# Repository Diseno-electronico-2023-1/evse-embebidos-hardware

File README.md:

# evse-embebidos-hardware
Cada grupo crea una rama para su PCB, cuando acaben hacen merge a la rama

Para crear una rama:

git checkout -b branch-name

Donde branch-name es el nombre de la rama Ej: Potencia

Una vez que estan en la nueva rama pueden subir sus cambios con:

git add .

git commit -m "Descripción de sus cambios"

git push -u origin branch-name

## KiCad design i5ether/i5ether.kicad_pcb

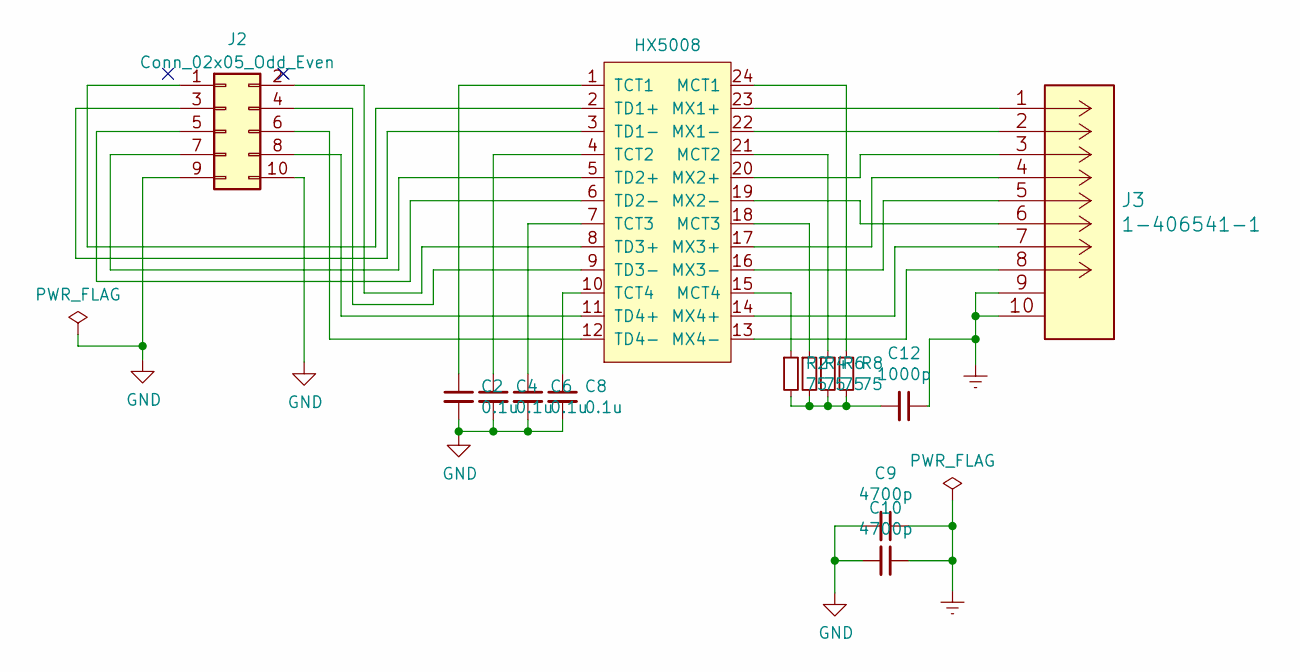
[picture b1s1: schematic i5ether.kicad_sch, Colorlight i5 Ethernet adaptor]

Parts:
C2, C4, C6, C8: 0.1u; C_0402_1005Metric
C9, C10: 4700p; R_1812_4532Metric
C12: 1000p; C_0402_1005Metric
J2: Conn_02x05_Odd_Even; PinHeader_2x05_P2.54mm_Horizontal
J3: 1-406541-1
R2, R4, R6, R8: 75; R_0402_1005Metric
T2: HX5008; HX5008NL

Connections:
Earth: C9.1, C10.1, C12.1, J3.9 (SHIELD), J3.10 (SHIELD)
GND: C2.2, C4.2, C6.2, C8.2, C9.2, C10.2, J2.9, J2.10
unnamed: C12.2, R2.2, R4.2, R6.2, R8.2
unnamed: J2.1, T2.2 (TD1+)
unnamed: J2.2, T2.8 (TD3+)
unnamed: J2.3, T2.3 (TD1-)
unnamed: J2.4, T2.9 (TD3-)
unnamed: J2.5, T2.6 (TD2-)
unnamed: J2.6, T2.12 (TD4-)
unnamed: J2.7, T2.5 (TD2+)
unnamed: J2.8, T2.11 (TD4+)
unnamed: R8.1, T2.24 (MCT1)
unnamed: R6.1, T2.21 (MCT2)
unnamed: R4.1, T2.18 (MCT3)
unnamed: R2.1, T2.15 (MCT4)
unnamed: J3.1, T2.23 (MX1+)
unnamed: J3.2, T2.22 (MX1-)
unnamed: J3.3, T2.20 (MX2+)
unnamed: J3.6, T2.19 (MX2-)
unnamed: J3.4, T2.17 (MX3+)
unnamed: J3.5, T2.16 (MX3-)
unnamed: J3.7, T2.14 (MX4+)
unnamed: J3.8, T2.13 (MX4-)
unnamed: C2.1, T2.1 (TCT1)
unnamed: C4.1, T2.4 (TCT2)
unnamed: C6.1, T2.7 (TCT3)
unnamed: C8.1, T2.10 (TCT4)

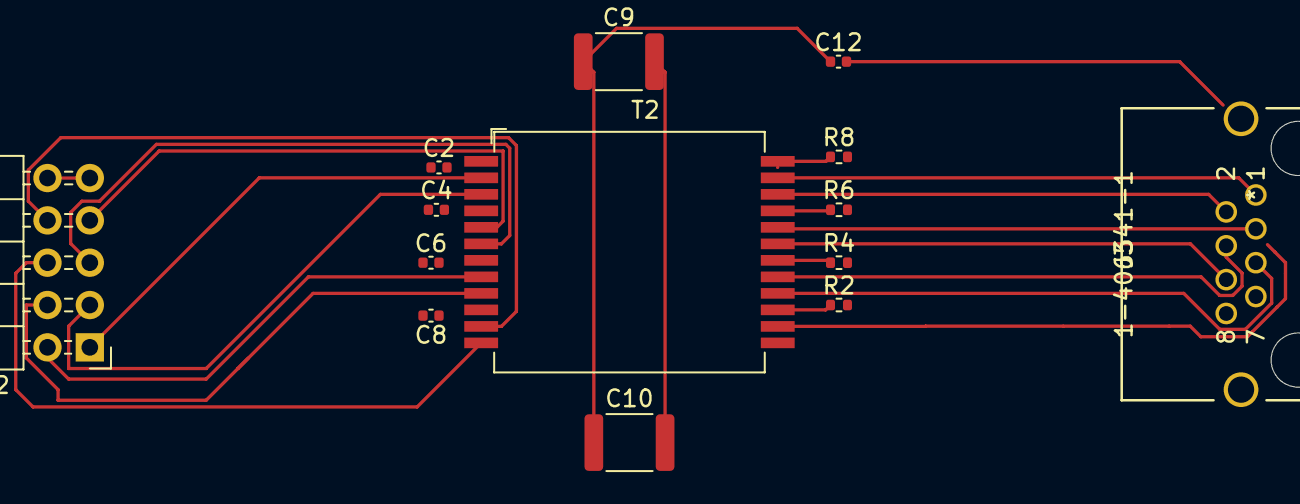
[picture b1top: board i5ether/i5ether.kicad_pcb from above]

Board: 2 copper layers, 14 parts (0 on the bottom side), 27 nets.

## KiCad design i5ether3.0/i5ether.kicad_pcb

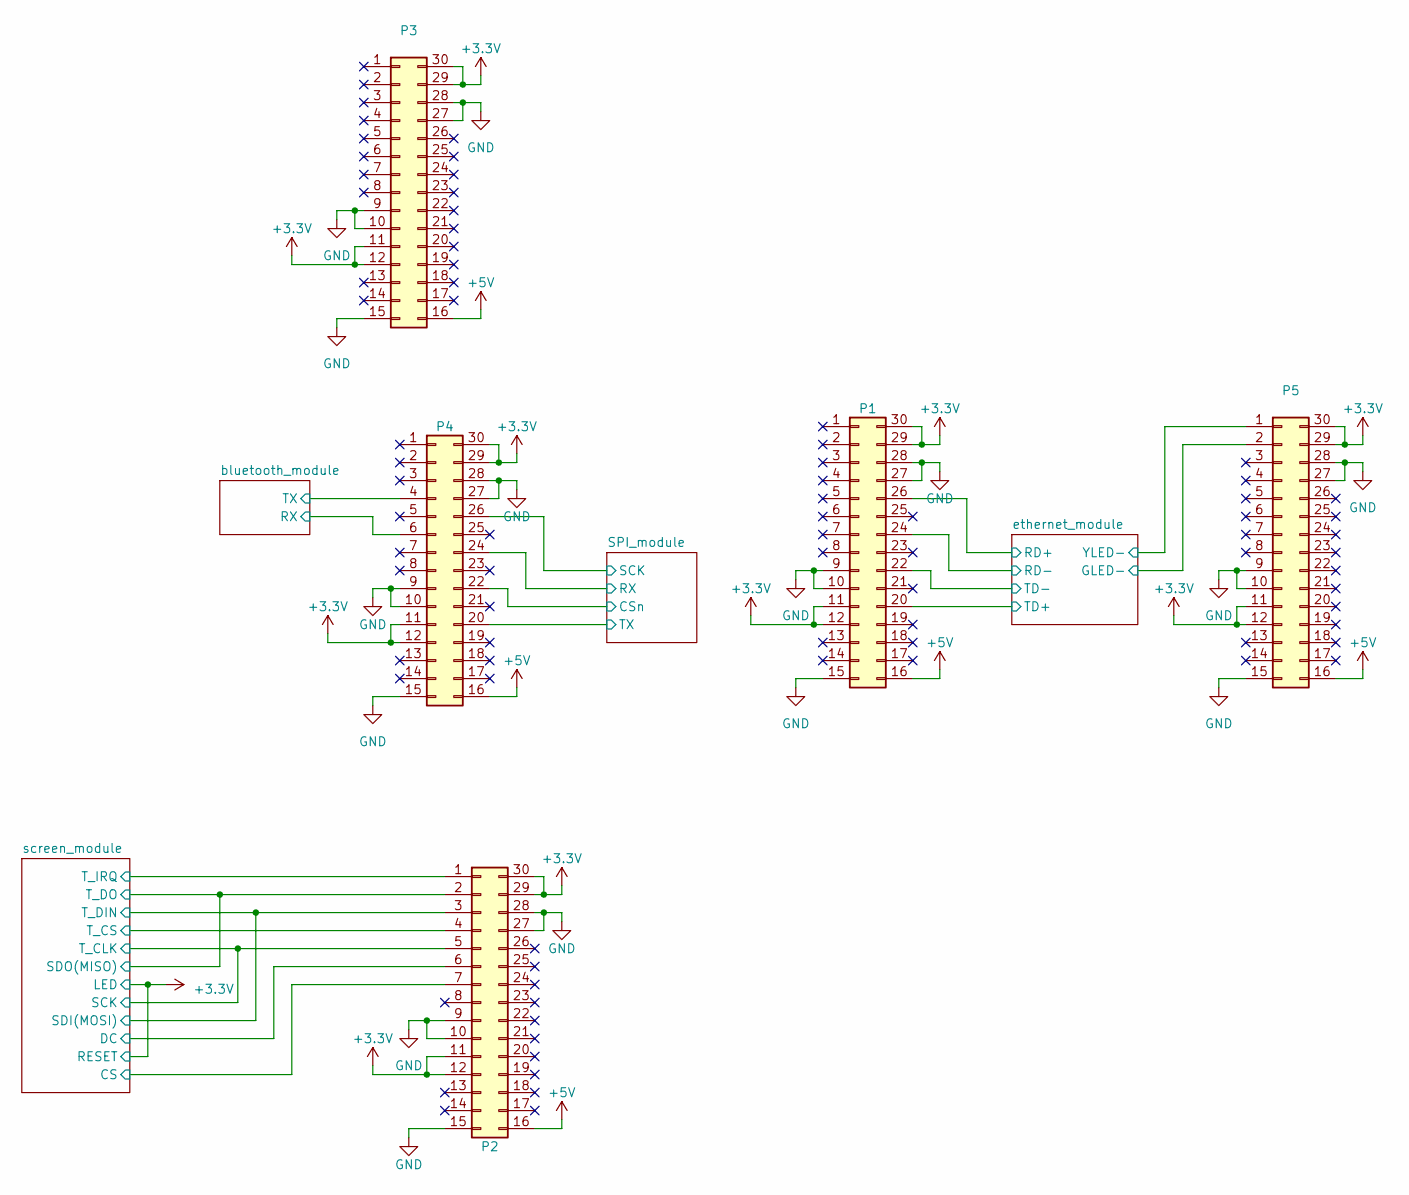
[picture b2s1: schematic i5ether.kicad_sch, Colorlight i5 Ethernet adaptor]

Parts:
P1, P2, P3, P4, P5: Conn_02x15_Counter_Clockwise; PinHeader_2x15_P2.54mm_Vertical

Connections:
+3.3V: P1.11, P1.12, P1.29, P1.30, P2.11, P2.12, P2.29, P2.30, P3.11, P3.12, P3.29, P3.30, P4.11, P4.12, P4.29, P4.30, P5.11, P5.12, P5.29, P5.30; also elsewhere on the board
+5V: P1.16, P2.16, P3.16, P4.16, P5.16
/SPI_module/CSn: P4.22; also elsewhere on the board
/SPI_module/RX: P4.24; also elsewhere on the board
/SPI_module/SCK: P4.26; also elsewhere on the board
/SPI_module/TX: P4.20; also elsewhere on the board
/bluetooth_module/RX: P4.6; also elsewhere on the board
/bluetooth_module/TX: P4.4; also elsewhere on the board
/ethernet_module/GLED-: P5.2; also elsewhere on the board
/ethernet_module/RD+: P1.26; also elsewhere on the board
/ethernet_module/RD-: P1.24; also elsewhere on the board
/ethernet_module/TD+: P1.20; also elsewhere on the board
/ethernet_module/TD-: P1.22; also elsewhere on the board
/ethernet_module/YLED-: P5.1; also elsewhere on the board
/screen_module/CS: P2.7; also elsewhere on the board
/screen_module/DC: P2.6; also elsewhere on the board
/screen_module/SCK: P2.5; also elsewhere on the board
/screen_module/SDI(MOSI): P2.3; also elsewhere on the board
/screen_module/SDO(MISO): P2.2; also elsewhere on the board
/screen_module/T_CS: P2.4; also elsewhere on the board
/screen_module/T_IRQ: P2.1; also elsewhere on the board
GND: P1.9, P1.10, P1.15, P1.27, P1.28, P2.9, P2.10, P2.15, P2.27, P2.28, P3.9, P3.10, P3.15, P3.27, P3.28, P4.9, P4.10, P4.15, P4.27, P4.28, P5.9, P5.10, P5.15, P5.27, P5.28; also elsewhere on the board

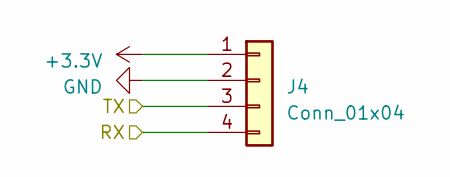
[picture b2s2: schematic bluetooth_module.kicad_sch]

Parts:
J4: Conn_01x04; PinSocket_1x04_P2.54mm_Horizontal

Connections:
+3.3V: J4.1; also elsewhere on the board
/bluetooth_module/RX: J4.4; also elsewhere on the board
/bluetooth_module/TX: J4.3; also elsewhere on the board
GND: J4.2; also elsewhere on the board

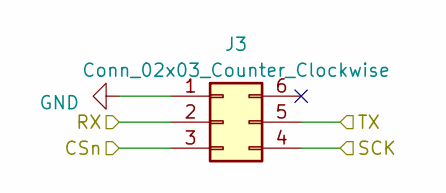
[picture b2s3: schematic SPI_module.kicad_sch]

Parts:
J3: Conn_02x03_Counter_Clockwise; IDC-Header_2x04_P2.54mm_Vertical

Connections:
/SPI_module/CSn: J3.3; also elsewhere on the board
/SPI_module/RX: J3.2; also elsewhere on the board
/SPI_module/SCK: J3.4; also elsewhere on the board
/SPI_module/TX: J3.5; also elsewhere on the board
GND: J3.1; also elsewhere on the board

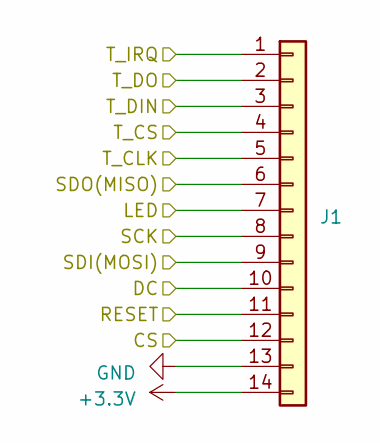
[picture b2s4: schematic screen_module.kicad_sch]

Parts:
J1: Conn_01x14; IDC-Header_2x08-1MP_P2.54mm_Latch6.5mm_Vertical

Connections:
+3.3V: J1.7, J1.11, J1.14; also elsewhere on the board
/screen_module/CS: J1.12; also elsewhere on the board
/screen_module/DC: J1.10; also elsewhere on the board
/screen_module/SCK: J1.5, J1.8; also elsewhere on the board
/screen_module/SDI(MOSI): J1.3, J1.9; also elsewhere on the board
/screen_module/SDO(MISO): J1.2, J1.6; also elsewhere on the board
/screen_module/T_CS: J1.4; also elsewhere on the board
/screen_module/T_IRQ: J1.1; also elsewhere on the board
GND: J1.13; also elsewhere on the board

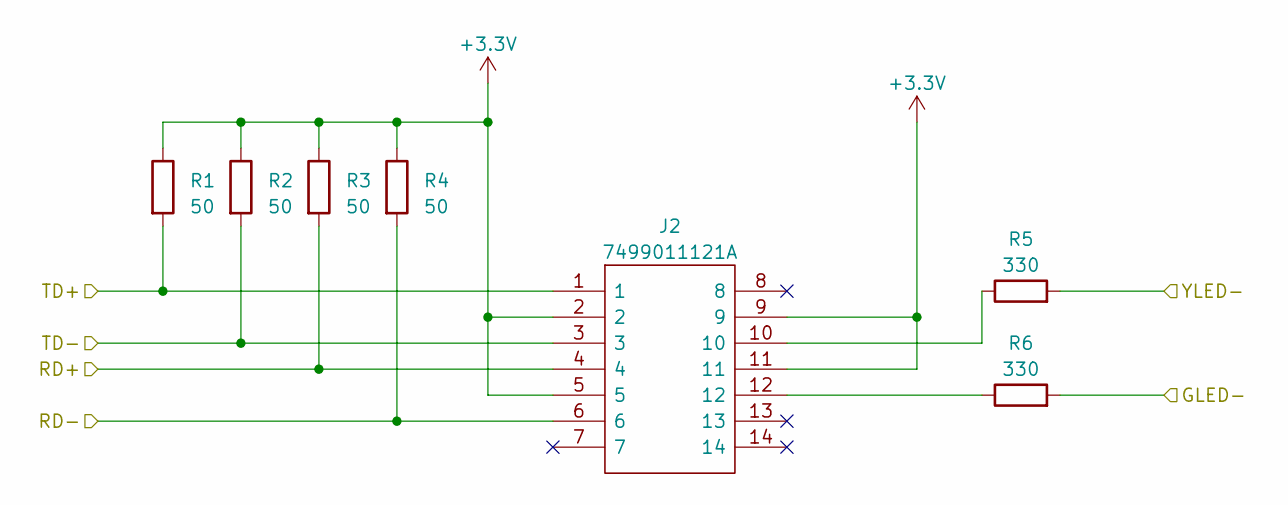
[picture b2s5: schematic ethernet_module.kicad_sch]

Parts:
J2: 7499011121A; Mouser Part Number 710-7499011121A
R1, R2, R3, R4: 50; R_0603_1608Metric_Pad0.98x0.95mm_HandSolder
R5, R6: 330; R_0603_1608Metric_Pad0.98x0.95mm_HandSolder

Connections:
+3.3V: J2.2, J2.5, J2.9, J2.11, R1.1, R2.1, R3.1, R4.1; also elsewhere on the board
/ethernet_module/GLED-: R6.2; also elsewhere on the board
/ethernet_module/RD+: J2.4, R3.2; also elsewhere on the board
/ethernet_module/RD-: J2.6, R4.2; also elsewhere on the board
/ethernet_module/TD+: J2.1, R1.2; also elsewhere on the board
/ethernet_module/TD-: J2.3, R2.2; also elsewhere on the board
/ethernet_module/YLED-: R5.2; also elsewhere on the board
unnamed: J2.10, R5.1
unnamed: J2.12, R6.1

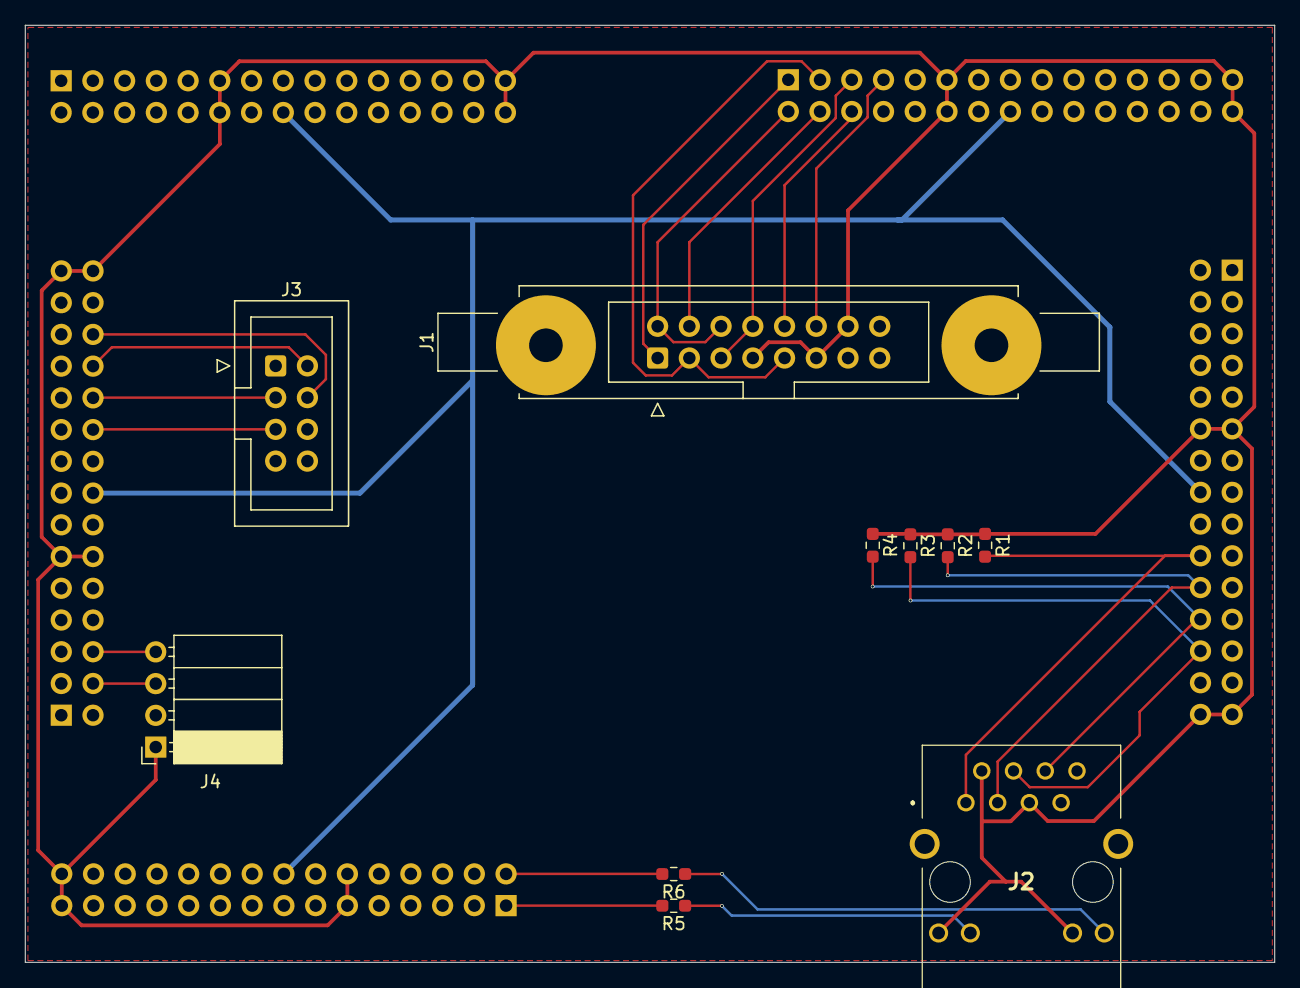
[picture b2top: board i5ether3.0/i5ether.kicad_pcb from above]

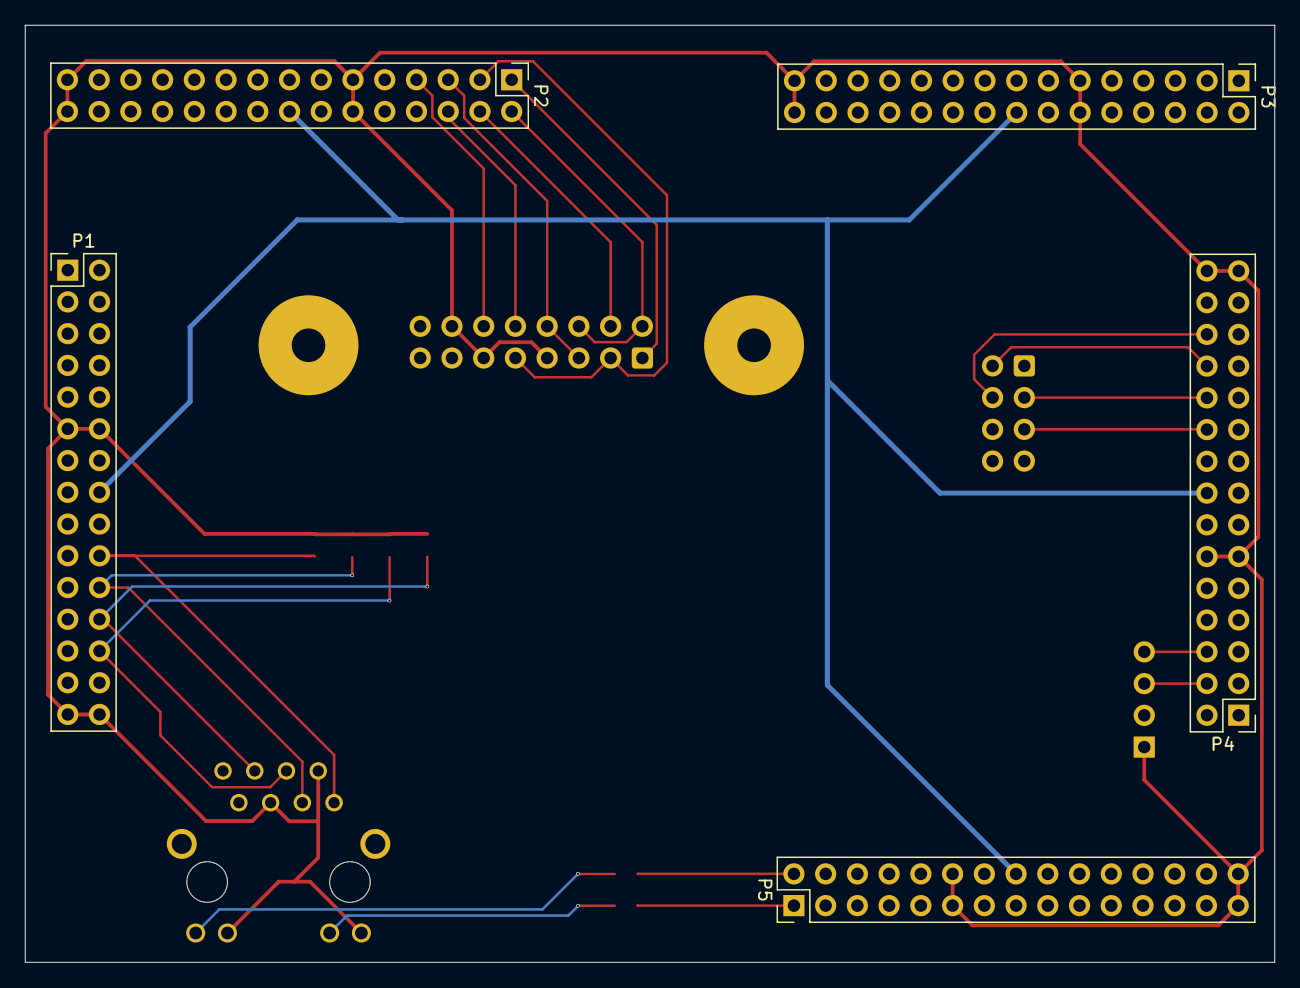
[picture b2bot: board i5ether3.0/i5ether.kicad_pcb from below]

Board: 2 copper layers, 100.0 x 75.0 mm, 15 parts (5 on the bottom side), 24 nets.

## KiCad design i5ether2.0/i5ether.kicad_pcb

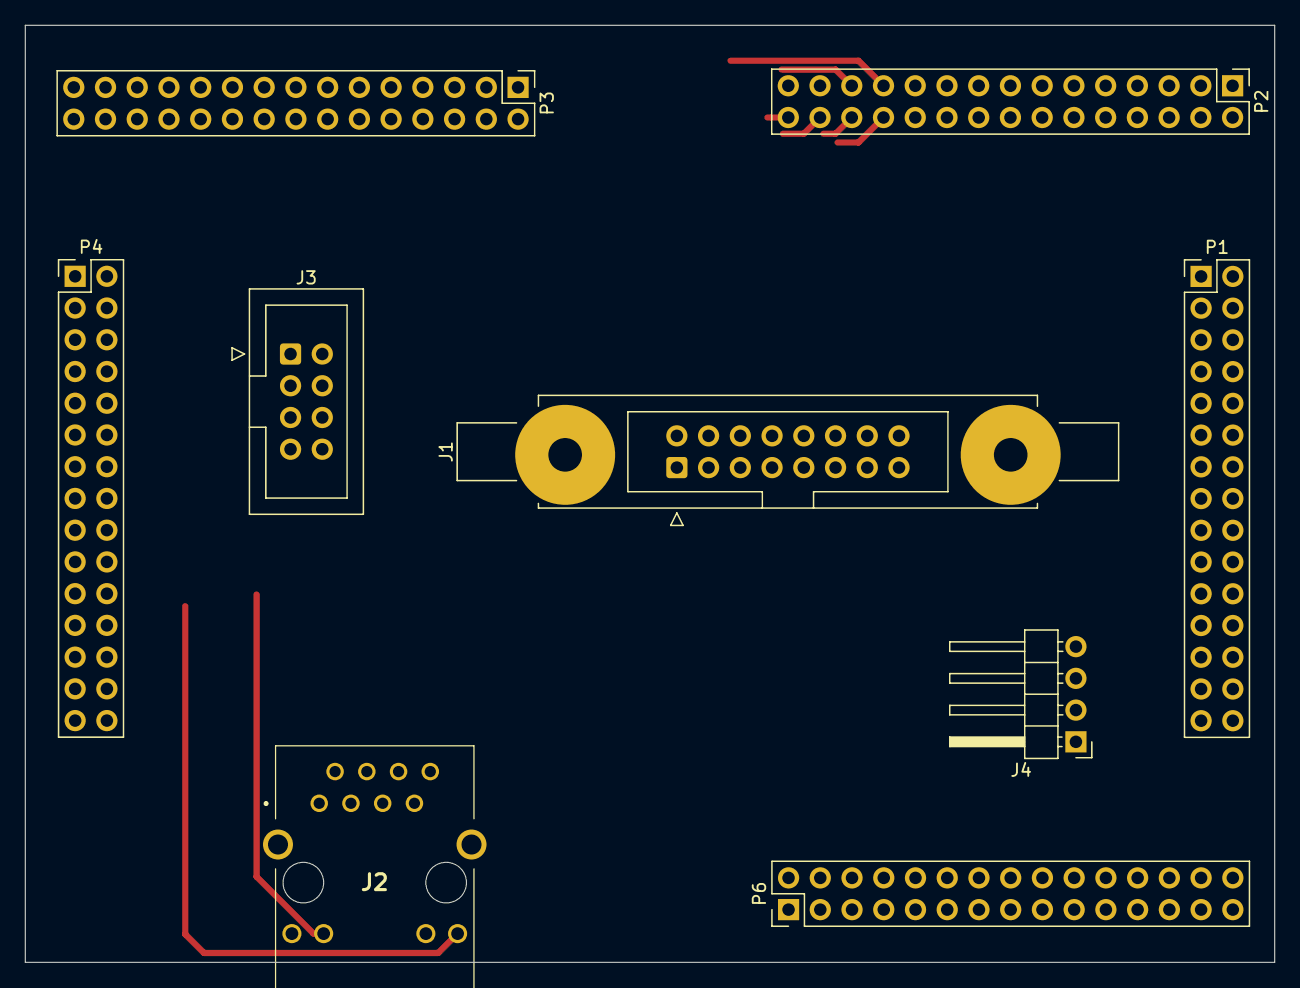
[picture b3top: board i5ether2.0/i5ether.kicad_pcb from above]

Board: 2 copper layers, 100.0 x 75.0 mm, 9 parts (0 on the bottom side), 26 nets.

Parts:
J1: Conn_01x14; IDC-Header_2x08-1MP_P2.54mm_Latch6.5mm_Vertical
J2: 7499011121A
J3: Conn_02x03_Counter_Clockwise; IDC-Header_2x04_P2.54mm_Vertical
J4: Conn_01x04; PinHeader_1x04_P2.54mm_Horizontal
P1, P2, P3, P4, P6: Conn_02x15_Counter_Clockwise; PinHeader_2x15_P2.54mm_Vertical

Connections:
+3.3V: J2.2, J2.5, J2.9, J2.11, J4.4
/SPI_module/CSn: J3.3, P4.12
/SPI_module/RX: J3.2, P4.10
/SPI_module/SCK: J3.4, P4.8
/SPI_module/TX: J3.5, P4.6
/bluetooth_module/RX: J4.1, P6.6
/bluetooth_module/TX: J4.2, P6.8
/ethernet_module/RD+: J2.4, P1.23
/ethernet_module/RD-: J2.6, P1.25
/ethernet_module/TD+: J2.1, P1.19
/ethernet_module/TD-: J2.3, P1.21
/screen_module/CS: J1.12, P2.6
/screen_module/DC: J1.10, P2.10
/screen_module/GND: J1.13, P2.4
/screen_module/LED: J1.7, P2.7
/screen_module/RESET: J1.11, P2.8
/screen_module/SCK: J1.8, P2.5
/screen_module/SDI(MOSI): J1.9, P2.12
/screen_module/SDO(MISO): J1.6, P2.9
/screen_module/T_CLK: J1.5, P2.11
/screen_module/T_CS: J1.4, P2.24
/screen_module/T_DIN: J1.3, P2.26
/screen_module/T_DO: J1.2, P2.28
/screen_module/T_IRQ: J1.1, P2.30
/screen_module/VCC: J1.14, P2.2
GND: J3.1, J4.3

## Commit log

2023-04-13 Huella placa Colorlighti5
2023-04-18 pasando a una capa
2023-04-18 Add files via upload
    Pcb ethernet 2 capas
2023-04-19 i5ether2.0
2023-04-24 Modulos
2023-04-24 Arreglos esquematico ethernet
2023-04-24 Essquematico con pantalla
2023-04-27 Avances en placa
2023-04-30 Pcb huellas y esquematico (sin resitensias)
2023-05-02 Add files via upload
    Conexiones realizadas
2023-05-02 Conexiones finales
    Conexiones finales
2023-05-08 PCB corecciones
2023-05-08 PCB Terminada
2023-05-11 PCB_Final
2023-05-12 Gerbers

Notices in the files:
parts and their libraries:
Copyright 2016 Accelerated Designs. All rights reserved.
